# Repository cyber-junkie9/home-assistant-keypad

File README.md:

# Home Assistant Keypad

A 9-key macro keypad for Home Assistant, running ESPHome. Every key is RGB backlit, and comes in
two variants: one that sits on a desk and one that mounts on a wall, with magnets or screws.

Desk variant:

Wall variant:

## Discord

Join the Discord if you want to follow along or ask questions: https://discord.gg/4yMsHbQQGn

## Waitlist

Want a pre-assembled one instead of building it yourself? Join the waitlist:
https://keypad.alex-labs.dev

## How to build it

### Tools required

- FDM 3D printer
- Soldering iron
- Phillips screwdriver
- 8 mm hollow gasket punch (wall variant only)
- Flush cutters

### Order components

The part names link to a search, so you can pick whichever shop you prefer.

| Part | Qty |
| --- | --- |
| [Gateron KS-33 low profile switches](https://www.google.com/search?q=Gateron+KS-33+low+profile+switch) | 9 |
| [Low profile keycaps](https://www.google.com/search?q=Gateron+KS-33+low+profile+keycaps) | 9 |
| [Seeed Studio XIAO ESP32C6](https://www.google.com/search?q=Seeed+Studio+XIAO+ESP32C6) | 1 |
| [SK6812MINI-E RGB LED, 3 mA](https://www.google.com/search?q=SK6812MINI-E+RGB+LED+3mA) | 9 |
| [74AHCT1G125GW,125 level shifter](https://www.google.com/search?q=74AHCT1G125GW%2C125) | 1 |
| [Ceramic capacitor 100 nF 50 V, 0805](https://www.google.com/search?q=ceramic+capacitor+100nF+50V+0805) | 10 |
| [Resistor 330 Ω, 0805](https://www.google.com/search?q=resistor+330+ohm+0805+SMD) | 1 |
| [M2 × 3 × 3 mm heat-set threaded inserts](https://www.google.com/search?q=M2+3x3mm+heat+set+threaded+insert) | 4 |
| [M2 × 6 mm countersunk Phillips screws](https://www.google.com/search?q=M2+6mm+countersunk+phillips+screw) | 4 |

For the wall-mounted variant you also need:

| Part | Qty |
| --- | --- |
| [Self-adhesive silicone rubber sheet, 1 mm](https://www.google.com/search?q=self+adhesive+silicone+rubber+sheet+1mm) | 1 |
| [Disc magnet Ø 10 mm, height 3 mm](https://www.google.com/search?q=disc+magnet+10mm+x+3mm) | 4 |

The keycaps I used are [these ones](https://nl.aliexpress.com/item/1005011938286189.html), variants
`B-A1 V2` and `W-A2 V2`.

The XIAO usually ships with pin headers. You need two 7-pin strips, so keep them.

### Order PCB

The board is 53 × 53 mm, 2 layers. Any fab house will work, but these instructions are for JLCPCB.

1. Download `gerber.zip`. Don't unzip it.
2. Go to [jlcpcb.com](https://jlcpcb.com), click **Order now** / **Add gerber file** and upload
   the zip.
3. Set the options below. Anything not listed is already correct at its default, leave it alone.
4. Save to cart and pick a shipping method at checkout.

| Option | Setting |
| --- | --- |
| Base Material | FR-4 |
| Layers | 2 |
| Dimensions | 53 × 53 (filled in automatically) |
| PCB Qty | 5 |
| Different Design | 1 |
| Delivery Format | Single PCB |
| PCB Thickness | 1.6 mm |
| Material Type | FR4 TG135 |
| Surface Finish | HASL (with lead) or Lead Free |
| Outer Copper Weight | 1 oz |
| Via Covering | Tented |
| Min via hole size | 0.3 mm / (0.4/0.45 mm) |
| Board Outline Tolerance | ±0.2 mm (Regular) |
| High-spec Options | leave as-is (all "No") |

Notes:

- 5 boards is the minimum order. You only need one, so you will have spares.
- Colour and silkscreen are cosmetic. Green is the fastest to produce.

### Print the enclosure

The STL files are in the `enclosure` folder. Pick `desk` or `wall` depending on the variant you
want. The wall variant also needs 4 magnet plugs.

I included an OrcaSlicer project with all the parameters already set:
`enclosure/keypad-orca-slicer.3mf`. It contains both variants, so disable the parts you don't need
before slicing.

The parts are designed to be printed in this orientation. Nothing needs supports.

My settings:

| | |
| --- | --- |
| Printer | Bambu Lab P1S, 0.4 mm nozzle |
| Process | 0.16mm High Quality @BBL X1C |
| Filament | PLA |
| Build plate | Textured PEI |

If you slice the STL files yourself instead, these are the settings that matter:

| Setting | Value |
| --- | --- |
| Layer height | 0.16 mm (0.2 mm first layer) |
| Wall loops | 3 |
| Top / bottom shell layers | 6 / 4 |
| Sparse infill | 25%, rectilinear |
| Nozzle temperature | 220 °C |
| Bed temperature | 55 °C |
| Supports | off |
| Elephant foot compensation | 0.15 mm |

**IMPORTANT:** the top plates and the magnet plugs print at 100% infill, the bottom parts stay
at 25%.

Tolerances are tight. If the board doesn't drop into the top shell, your parts have most likely
shrunk. Scale them up a little, start with 100.5%, and reprint. In my case the original scale
worked fine.

### PCB assembly

**Do this in exactly this order.**

#### 1. Solder all the SMD components on the PCB

All the SMD parts go on the front side of the board, the switches go on the back later. The photos
below show where each part sits.

9 × SK6812MINI-E LED:

**IMPORTANT:** the LEDs go in one orientation only. The package has one corner cut at an angle, and
the board has a small triangle printed next to every LED footprint. The cut corner points at the
triangle. All 9 LEDs face the same way, so before you solder, check that all nine cut corners point
in the same direction.

The LEDs are daisy chained, so a single LED turned the wrong way breaks the chain: that one and
every LED after it stay dark.

10 × 100 nF capacitor:

R1 (330 Ω) and U1 (74AHCT1G125GW), both in the top left corner:

#### 2. Solder the two pin headers

Put the two 7-pin headers into the U2 footprint from the front, pins pointing up, and solder them
from the back.

**IMPORTANT:** solder the headers to the PCB only. Don't solder the XIAO module onto them yet, it
goes on in step 4.

#### 3. Solder the switches

**IMPORTANT:** install all the switches in the top shell first, then put the PCB in the shell and
solder them in place.

Press all 9 switches into the top shell from the inside until they click:

Then drop the PCB onto the switch pins, SMD side up. Each switch has two pins that come through the
board, so solder all 18:

#### 4. Solder the controller module

Push the XIAO onto the two headers, with the USB-C connector pointing at the slot in the shell wall,
and solder both rows, 14 joints. Trim the header pins with the flush cutters.

### Assemble the enclosure

#### Desk variant

The desk variant is the simplest one. Press the heat-set inserts into the four holes. A soldering
iron with a conical tip works well for this.

Then screw the top and bottom parts together with the 4 screws. They go in from the front, between
the switches.

Install the keycaps and it's done!

#### Wall variant

The wall variant uses the same inserts and the same 4 screws to hold the two parts together. On top
of that it has 4 beds for the magnets and 4 printed caps that hold the magnets in place.

The beds are the corner holes. The 2 smaller holes in the middle are for the wall screws.

Put the magnets in place and screw the caps in. The caps have a slot, so a flat screwdriver works.

Finally, add the silicone rubber pads on the other side. Punch them out of the silicone sheet with
the 8 mm gasket punch.

### Build and flash ESPHome

ESPHome is a tool that turns a YAML file into firmware for ESP32 boards, no coding needed.
`esphome.yaml` in this repo is not a whole config, it is only the part that describes the 9 keys and
the 9 LEDs. You paste it under the config ESPHome writes for you.

1. In Home Assistant go to **Settings → Add-ons → Add-on store**, install **ESPHome Device
   Builder**, start it and open it.
2. Press **+ New device**, call it `keypad` and pick **Seeed Studio XIAO ESP32C6**. It asks for your
   wifi once and remembers it.
3. Open the new device with **Edit**, put the cursor at the very bottom and paste the whole contents
   of `esphome.yaml` there. Change nothing above it: the generated API key, OTA and wifi blocks are
   yours, and the file doesn't touch them. See below for what you should end up with.
4. Plug the keypad into your computer with a USB-C cable, press **Install** and choose **Plug into
   the computer running ESPHome Device Builder**. Later updates go over wifi, no cable needed.
5. Home Assistant finds the keypad by itself. Go to **Settings → Devices & services** and confirm
   it.

This is what the wizard writes in step 2. Your name, key and hotspot password will be different.
Leave all of it alone and paste at the bottom:

```yaml
esphome:
  name: keypad
  friendly_name: keypad

esp32:
  variant: esp32c6
  flash_size: 4MB
  framework:
    type: esp-idf

logger:

api:
  encryption:
    key: "the key generated for you, don't share it"

ota:
  - platform: esphome

wifi:
  ssid: !secret wifi_ssid
  password: !secret wifi_password
  ap:
    ssid: keypad Fallback Hotspot
    password: "the password generated for you"

captive_portal:

# ---> everything in esphome.yaml goes here, from this line down <---
```

You get 18 entities:

| Entity | What it does |
| --- | --- |
| Key 1 … Key 9 | fires `press` or `long_press` |
| LED 1 … LED 9 | RGB light, one per key |

In an automation, trigger on a key entity and branch on its `event_type` attribute. The hold time is
1 second; change `long_press_ms` at the top of the config to adjust it.

## License

[CC BY-NC-SA 4.0](https://creativecommons.org/licenses/by-nc-sa/4.0/). Build it, modify it, share
it, but not commercially, and credit the original. See [LICENSE](LICENSE) for the details and for
the third-party footprint libraries used in the KiCad project.

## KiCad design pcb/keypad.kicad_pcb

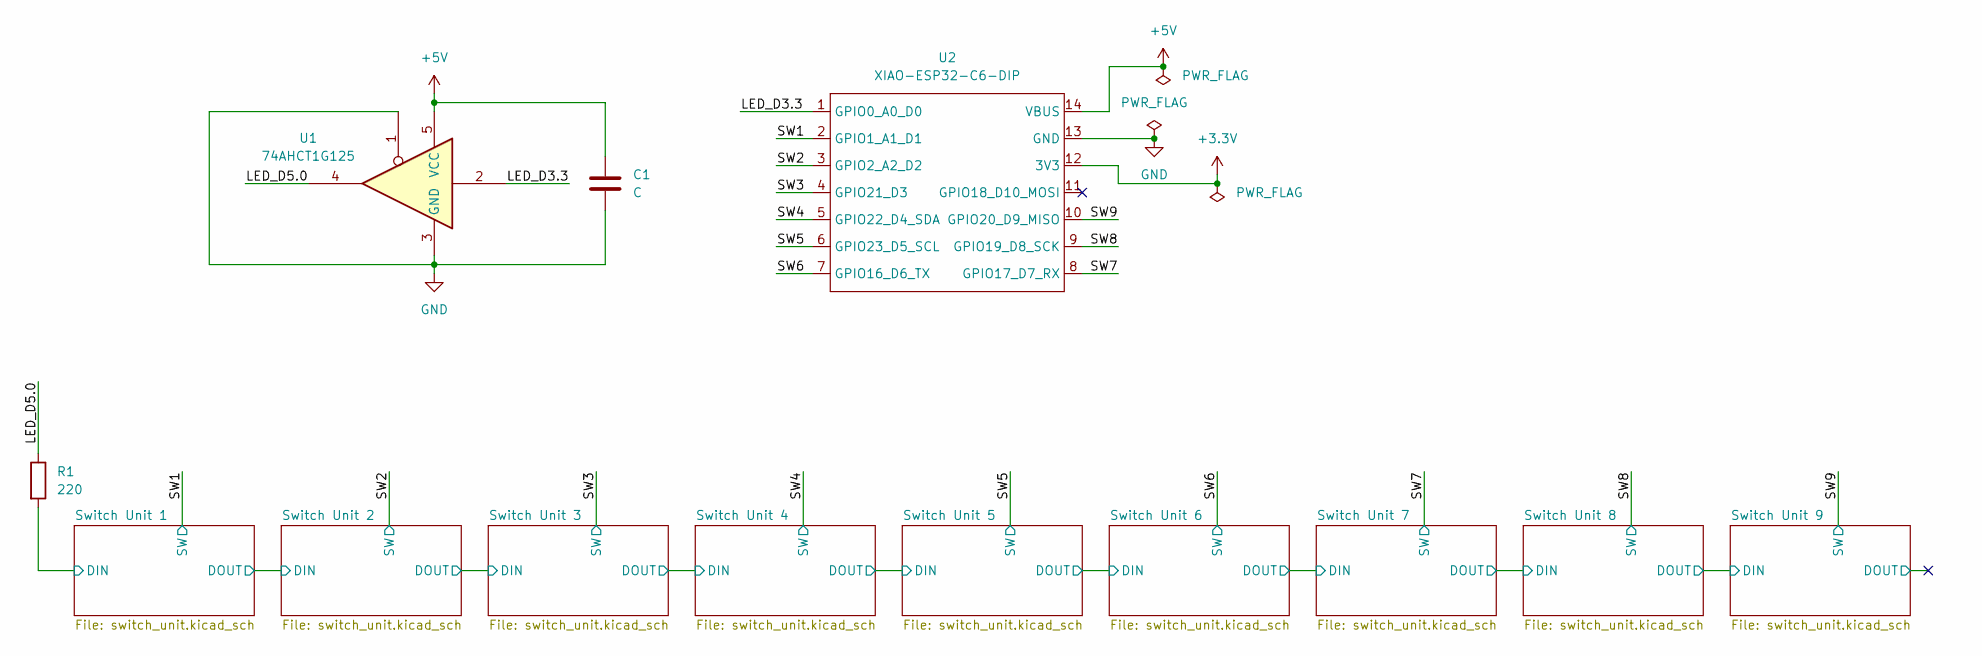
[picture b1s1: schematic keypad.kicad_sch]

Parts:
C1: C; C_0805_2012Metric
R1: 220; R_0805_2012Metric
U1: 74AHCT1G125; SOT-353_SC-70-5
U2: XIAO-ESP32-C6-DIP

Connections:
+3.3V: U2.12 (3V3)
+5V: C1.1, U1.5 (VCC), U2.14 (VBUS); also elsewhere on the board
/LED_D3.3: U1.2, U2.1 (GPIO0_A0_D0)
/LED_D5.0: R1.1, U1.4
/SW1: U2.2 (GPIO1_A1_D1); also elsewhere on the board
/SW2: U2.3 (GPIO2_A2_D2); also elsewhere on the board
/SW3: U2.4 (GPIO21_D3); also elsewhere on the board
/SW4: U2.5 (GPIO22_D4_SDA); also elsewhere on the board
/SW5: U2.6 (GPIO23_D5_SCL); also elsewhere on the board
/SW6: U2.7 (GPIO16_D6_TX); also elsewhere on the board
/SW7: U2.8 (GPIO17_D7_RX); also elsewhere on the board
/SW8: U2.9 (GPIO19_D8_SCK); also elsewhere on the board
/SW9: U2.10 (GPIO20_D9_MISO); also elsewhere on the board
/Switch Unit 1/DIN: R1.2; also elsewhere on the board
GND: C1.2, U1.1, U1.3 (GND), U2.13 (GND); also elsewhere on the board

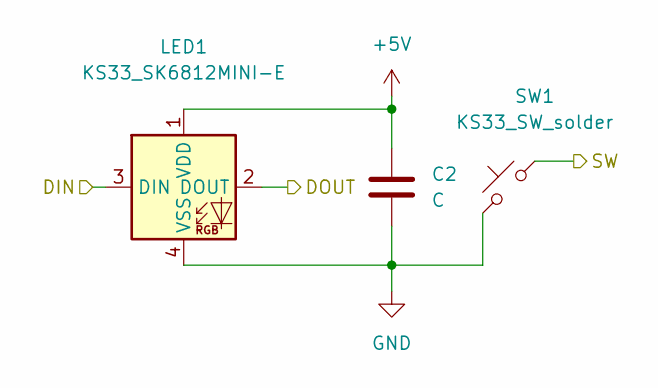
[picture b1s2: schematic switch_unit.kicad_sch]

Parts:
C2: C; C_0805_2012Metric
LED1: KS33_SK6812MINI-E; LED_KS33_6028R
SW1: KS33_SW_solder; SW_KS33_1u

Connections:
+5V: C2.1, LED1.1 (VDD); also elsewhere on the board
/SW1: SW1.2; also elsewhere on the board
/Switch Unit 1/DIN: LED1.3 (DIN); also elsewhere on the board
/Switch Unit 1/DOUT: LED1.2 (DOUT); also elsewhere on the board
GND: C2.2, LED1.4 (VSS), SW1.1; also elsewhere on the board

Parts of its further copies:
C3, C4, C5, C6, C7, C8, C9, C10: C; C_0805_2012Metric
LED2, LED3, LED4, LED5, LED6, LED7, LED8, LED9: KS33_SK6812MINI-E; LED_KS33_6028R
SW2, SW3, SW4, SW5, SW6, SW7, SW8, SW9: KS33_SW_solder; SW_KS33_1u

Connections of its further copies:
+5V: C3.1, C4.1, C5.1, C6.1, C7.1, C8.1, C9.1, C10.1, LED2.1 (VDD), LED3.1 (VDD), LED4.1 (VDD), LED5.1 (VDD), LED6.1 (VDD), LED7.1 (VDD), LED8.1 (VDD), LED9.1 (VDD); also elsewhere on the board
/SW2: SW2.2; also elsewhere on the board
/SW3: SW3.2; also elsewhere on the board
/SW4: SW4.2; also elsewhere on the board
/SW5: SW5.2; also elsewhere on the board
/SW6: SW6.2; also elsewhere on the board
/SW7: SW7.2; also elsewhere on the board
/SW8: SW8.2; also elsewhere on the board
/SW9: SW9.2; also elsewhere on the board
/Switch Unit 1/DOUT: LED2.3 (DIN); also elsewhere on the board
/Switch Unit 2/DOUT: LED2.2 (DOUT), LED3.3 (DIN)
/Switch Unit 3/DOUT: LED3.2 (DOUT), LED4.3 (DIN)
/Switch Unit 4/DOUT: LED4.2 (DOUT), LED5.3 (DIN)
/Switch Unit 5/DOUT: LED5.2 (DOUT), LED6.3 (DIN)
/Switch Unit 6/DOUT: LED6.2 (DOUT), LED7.3 (DIN)
/Switch Unit 7/DOUT: LED7.2 (DOUT), LED8.3 (DIN)
/Switch Unit 8/DOUT: LED8.2 (DOUT), LED9.3 (DIN)
/Switch Unit 9/DOUT: LED9.2 (DOUT)
GND: C3.2, C4.2, C5.2, C6.2, C7.2, C8.2, C9.2, C10.2, LED2.4 (VSS), LED3.4 (VSS), LED4.4 (VSS), LED5.4 (VSS), LED6.4 (VSS), LED7.4 (VSS), LED8.4 (VSS), LED9.4 (VSS), SW2.1, SW3.1, SW4.1, SW5.1, SW6.1, SW7.1, SW8.1, SW9.1; also elsewhere on the board

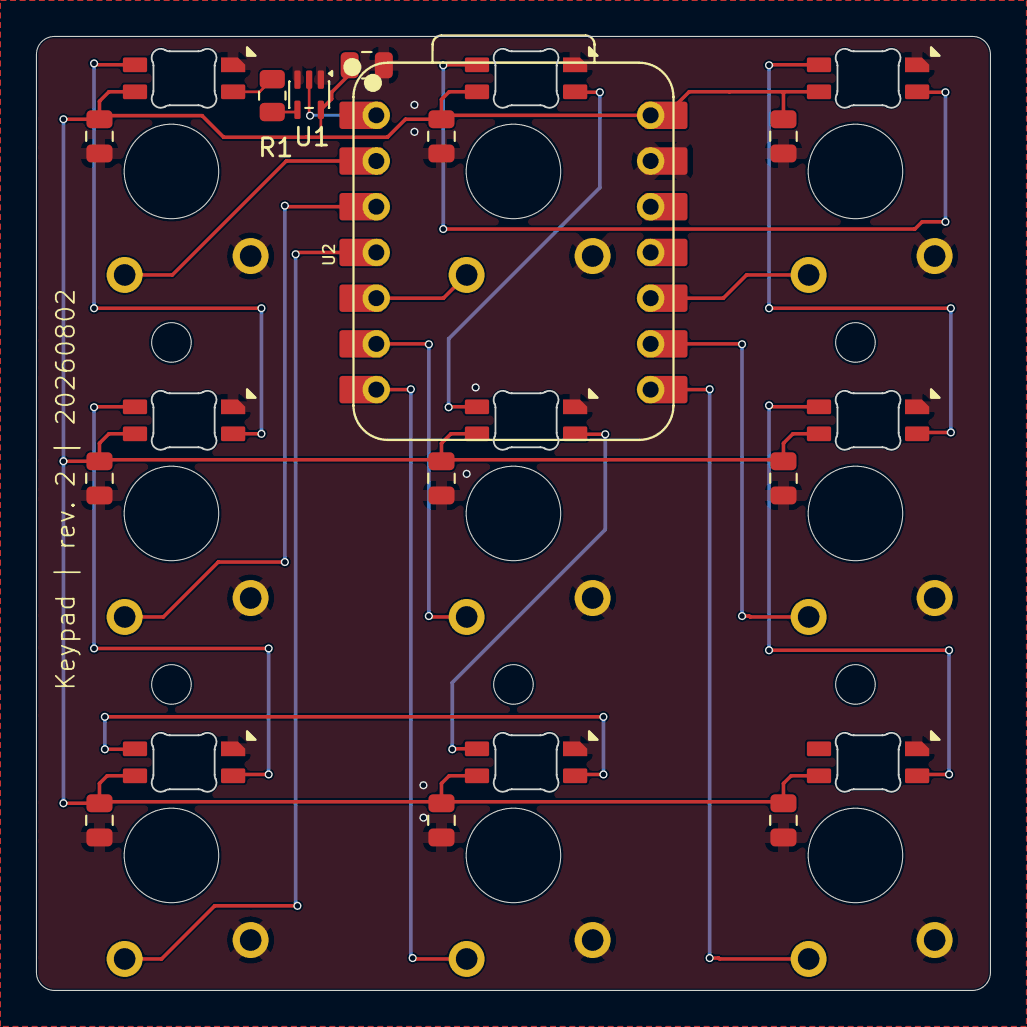
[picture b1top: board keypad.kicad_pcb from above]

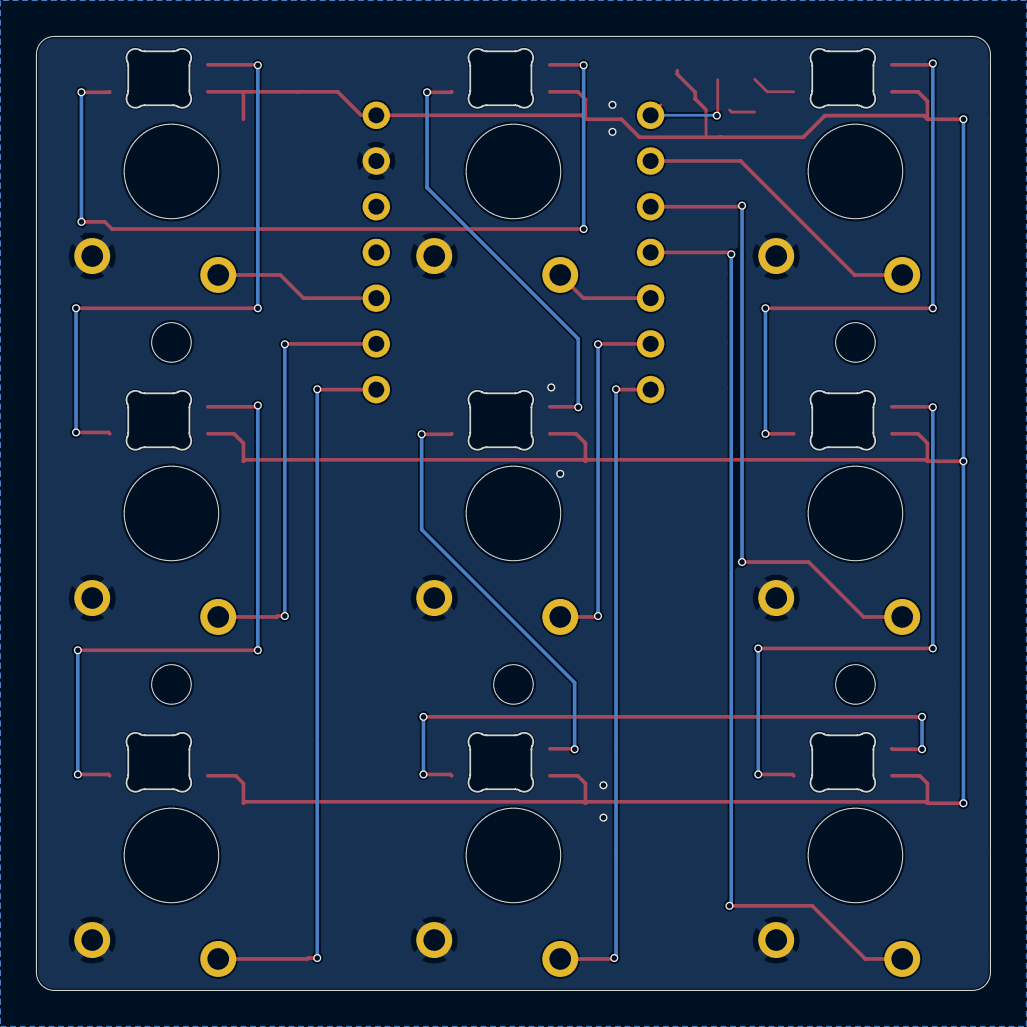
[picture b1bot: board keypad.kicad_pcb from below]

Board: 2 copper layers, 53.0 x 53.0 mm, 31 parts (9 on the bottom side), 22 nets.
